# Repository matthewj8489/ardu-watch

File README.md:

# ardu-watch
Arduino powered watch

Features:
- OLED display
- Real Time Clock
- USB->FTDI programming
- 3 pushbutton controls

AW-2 Future Additional Features
- Accel/Gyro/Magn sensors
- Bluetooth

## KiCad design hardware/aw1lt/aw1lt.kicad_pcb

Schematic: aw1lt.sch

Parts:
BT1: Battery_Cell; Coin_Cell_Retainer_3034
BZ1: Buzzer; Buzzer_ST-0402S
C1, C2, C3, C4: 1uF; C_0603
C5, C8, C10, C11: 0.1uF; C_0603
C6: 2.2uF; C_0603
C7: 4.7uF; C_0603
C9: 10uF; CP_Tantalum_Case-A_EIA-3216-18_Wave
D1: D; D_0805
J1: ISP_FTDI; Pin_Header_Straight_2x04_Pitch1.00mm_SMD
OLEDM1: SSD1306; SSD1306-FPC-foldover
Q1: Q_NPN_CBE; SOT-23
R1, R4, R5, R6: 10K; R_0603
R2: 390K; R_0603
R3: 180; R_0603
RN2: 1K; EXB38V
SW1, SW2, SW3: SW_Push; SW_SPST_B3U-3000P
U1: DS3231MZ; SOIC-8_3.9x4.9mm_Pitch1.27mm
U2: ATMEGA328P-AU; TQFP-32_7x7mm_Pitch0.8mm

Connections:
+3V3: BT1.1 (+), BZ1.1, C1.1, C4.1, C5.1, C9.1, C10.1, D1.1 (K), J1.2, OLEDM1.6 (VBAT), OLEDM1.9 (VDD), R1.1, R4.1, R5.1, R6.1, SW1.2, SW2.2, SW3.2, U1.4 (~RST), U1.6 (VBAT), U2.4 (VCC), U2.6 (VCC), U2.18 (AVCC)
A1: U2.23 ((PCINT8/ADC0)PC0)
A2: U2.25 ((PCINT10/ADC2)PC2)
A3: U2.26 ((PCINT11/ADC3)PC3)
A6: U2.19 (ADC6)
A7: U2.22 (ADC7)
CS: OLEDM1.13 (CS#), U2.14 ((PCINT2/OC1B/~SS~)PB2)
D8: OLEDM1.15 (C/D#), U2.12 ((PCINT0/CLKO/ICP1)PB0)
D9: OLEDM1.14 (RES#), U2.13 ((PCINT1/OC1A)PB1)
DTR: C11.2, J1.5
FS: U2.2 ((PCINT20/XCK/T0)PD4)
GND: BT1.2 (-), C1.2, C4.2, C5.2, C6.2, C7.2, C8.2, C9.2, C10.2, J1.6, OLEDM1.1 (NC), OLEDM1.8 (VSS), OLEDM1.10 (BS0), OLEDM1.11 (BS1), OLEDM1.12 (BS2), OLEDM1.16 (R/W#), OLEDM1.17 (E_RD#), OLEDM1.21 (DB3), OLEDM1.22 (DB4), OLEDM1.23 (DB5), OLEDM1.24 (DB6), OLEDM1.25 (DB7), OLEDM1.29 (VLSS), OLEDM1.30 (NC), Q1.3, R2.2, RN2.6, RN2.7, RN2.8, U1.2 (VCC), U1.5 (GND), U2.3 (GND), U2.5 (GND), U2.21 (GND)
INT0: R1.2, U1.3 (~INT~/SQW), U2.32 ((PCINT18/INT0)PD2)
INT1: U2.1 ((PCINT19/OC2B/INT1)PD3)
MISO: J1.1, U2.16 ((PCINT4/MISO)PB4)
MOSI: J1.4, OLEDM1.19 (DB1), U2.15 ((PCINT3/OC2A/MOSI)PB3)
unnamed: BZ1.2, D1.2 (A), Q1.1
unnamed: C2.1, OLEDM1.4 (CAP1P)
unnamed: C2.2, OLEDM1.5 (CAP1N)
unnamed: C3.1, OLEDM1.2 (CAP2P)
unnamed: C3.2, OLEDM1.3 (CAP2N)
unnamed: C6.1, OLEDM1.28 (VCC)
unnamed: C7.1, OLEDM1.27 (VCOMH)
unnamed: C8.1, U2.20 (AREF)
unnamed: C11.1, R4.2, U2.29 ((PCINT14/~RESET~)PC6)
unnamed: OLEDM1.26 (IREF), R2.1
unnamed: Q1.2, R3.1
PB0: RN2.3, SW1.1, U2.9 ((PCINT21/OC0B/T1)PD5)
PB1: RN2.2, SW2.1, U2.10 ((PCINT22/OC0A/AIN0)PD6)
PB2: RN2.1, SW3.1, U2.11 ((PCINT23/AIN1)PD7)
RXD: J1.7, U2.30 ((PCINT16/RXD)PD0)
SCK: J1.3, OLEDM1.18 (DB0), U2.17 ((PCINT5/SCK)PB5)
SCL: R6.2, U1.8 (SCL), U2.28 ((PCINT13/SCL/ADC5)PC5)
SDA: R5.2, U1.7 (SDA), U2.27 ((PCINT12/SDA/ADC4)PC4)
SPKR: R3.2, U2.24 ((PCINT9/ADC1)PC1)
TXD: J1.8, U2.31 ((PCINT17/TXD)PD1)

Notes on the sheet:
I2C 0x68 (0xD0/0xD1)
RTC
OLED 128x64
Pushbuttons (Active High)
Close To Atmega328p
Do internal resistors and Active Low? save on components...
Low Leakage
Buzzer Circuit

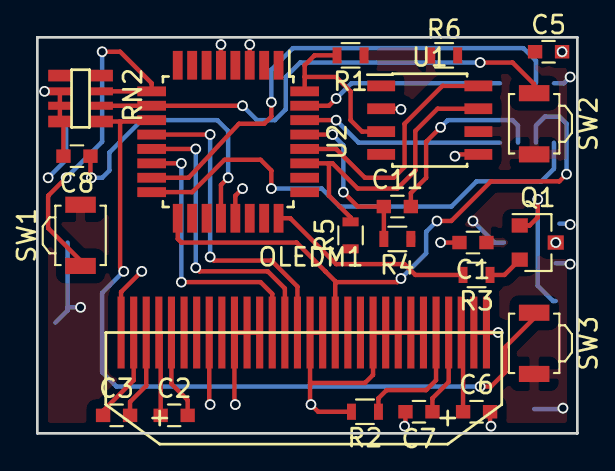
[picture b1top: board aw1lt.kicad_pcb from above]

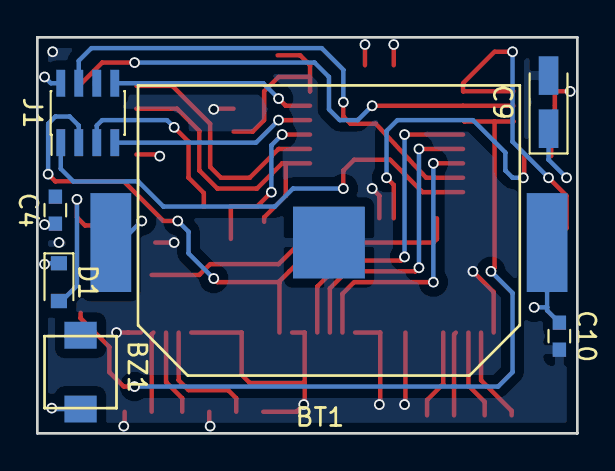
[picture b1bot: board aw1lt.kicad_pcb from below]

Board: 2 copper layers, 30.0 x 22.0 mm, 29 parts (7 on the bottom side), 29 nets.

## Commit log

2017-07-19 adding in the initial files
2017-07-19 adding test firmware and a dev doc
2017-07-21 added more to the schematic, filled in push buttons, mpu-9250
2017-07-21 adding a potential oled component
2017-07-25 finished up the oled. adding some usb->ftdi support...need more research on this
2017-07-25 adding datasheets
2017-07-26 added in the wiring for the USB->FTDI. it *should* also power the micro when the usb is plugged in
2017-07-26 a resistor value fix
2017-07-27 renaming
2017-07-27 moving to arduino folder
2017-07-28 adding more datasheets
2017-07-28 made a lot of changes. used kicad library component for ft231 made sure ft231 components looked correct
2017-07-28 added some features and future features details
2017-07-31 filled out the vusb/vbat switching circuit more
2017-08-01 adding the motor circuit control
2017-08-01 figured out the power supply circuitry. adding in caps close to the power supply to each IC
2017-08-02 added annotations
2017-08-03 added a ICSP connector for programming
2017-08-08 choosing more footprints for components
2017-08-17 doing some pcb work...also making a prototype case in scad
2017-08-25 decided to start with a light version of the watch, have been working on that schematic and pcb
2017-08-29 have a better connector put down for the ISP and FTDI pins. considering removing the power switching circuit and not connecting the vcc of those pins
2017-08-30 adding in a speaker, getting things fitting in the pcb
2017-09-01 additional work on the pcb, realized that the buttons can be inline with the circuit board and a case attachment can be used to push the buttons
2017-09-05 starting to set tracks down
2017-09-14 still trying to figure out this routing and placement...
2017-09-15 made the coin cell footprint more accurate, did some measurements so that i know how far the actual coin battery will be protruding from the retainer and where i can place components
2017-09-19 working on routing
2017-09-20 working on more routing, switched to 603 on most caps and resistors for more space. thinking of rotating the micro for better pin location...
2017-09-21 more routing, have a separate board for a rotated uc
2017-10-09 modified a bit of the layout, rotated some parts, got rid of a resistor network in favor of individual resistors for more flexibility
2017-10-10 making progress on routing
2017-10-11 have all the pins routed, now need to connect the grounds and power with copper pours
2018-04-19 some changes
